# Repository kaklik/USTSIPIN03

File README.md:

## USTSIPIN03 - Semiconductor based ionizing radiation dosimeter and spectrometer analog front-end

The USTSIPIN03 is developed as single board improved variant of the [PIND02](https://github.com/mlab-modules/PIND02) and [PCRD07](https://github.com/mlab-modules/PCRD07) modules from [MLAB.cz development system](https://www.mlab.cz/).  The analog front end is core part of the [AIRDOS04 cosmic radiation detector and dosimeter](https://github.com/UniversalScientificTechnologies/AIRDOS04).

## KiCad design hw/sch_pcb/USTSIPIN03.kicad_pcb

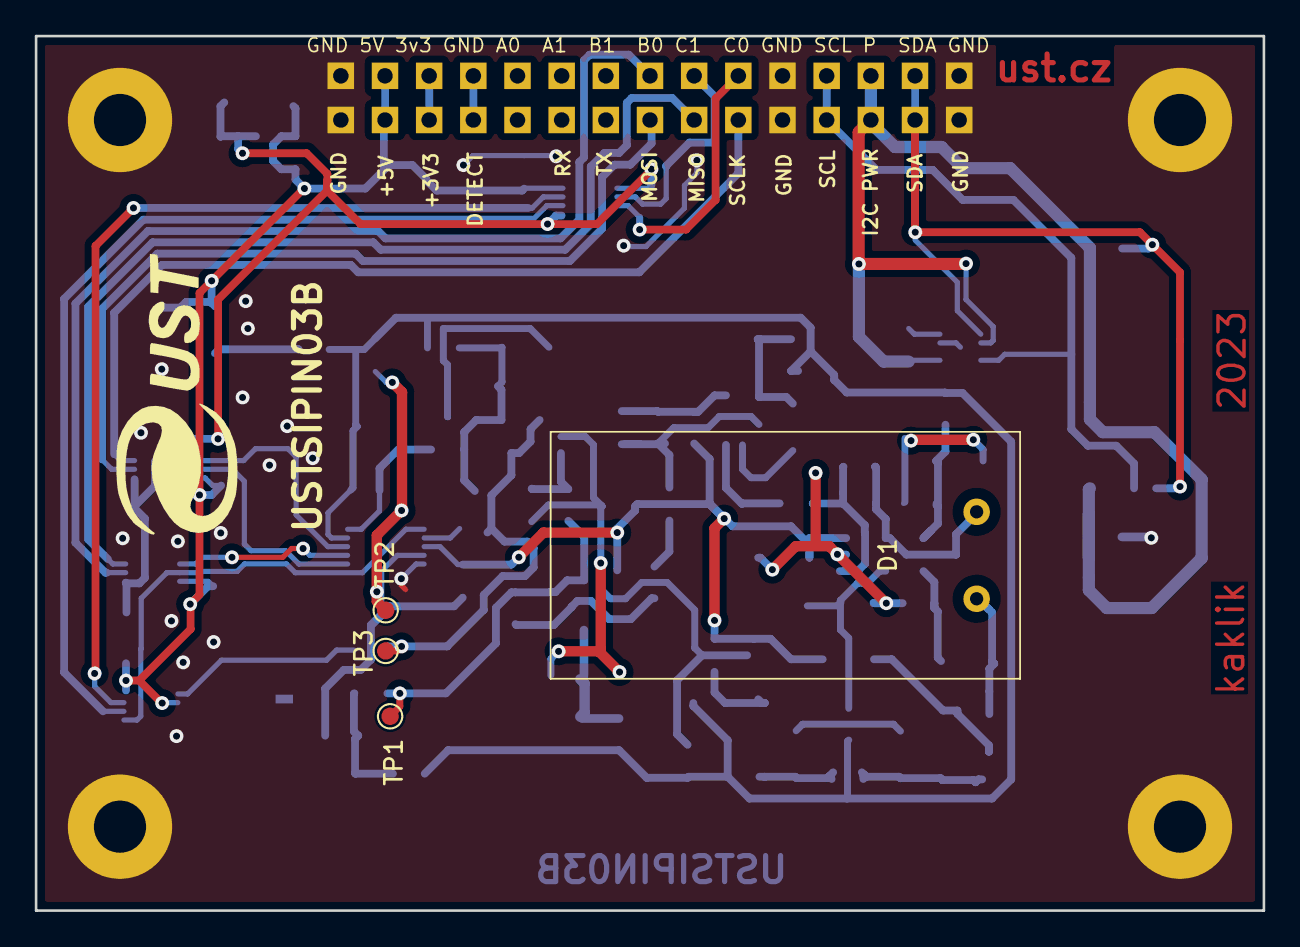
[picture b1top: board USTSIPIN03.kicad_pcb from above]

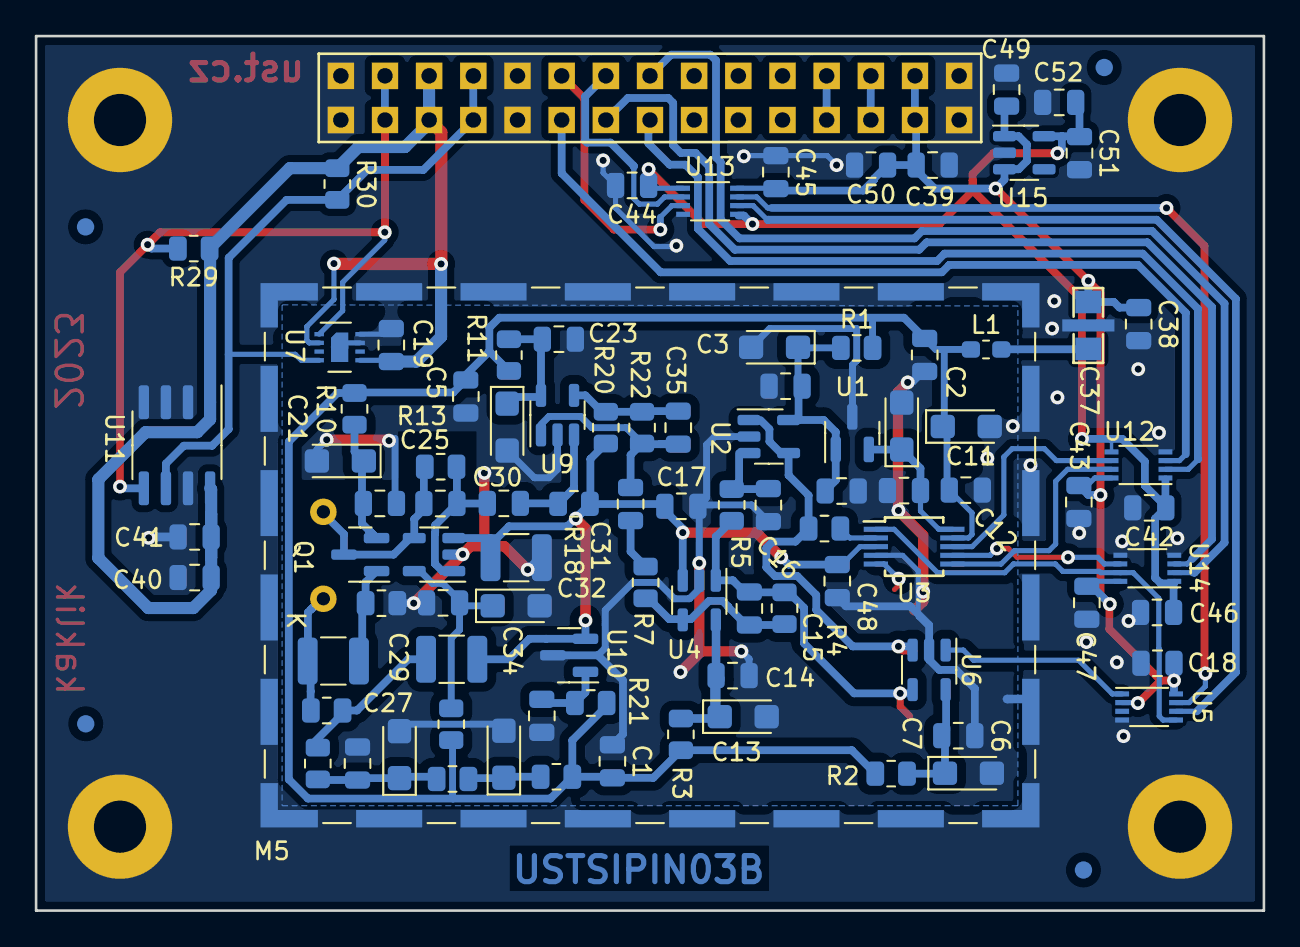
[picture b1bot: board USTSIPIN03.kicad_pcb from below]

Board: 2 copper layers, 70.6 x 50.3 mm, 107 parts (98 on the bottom side), 49 nets.

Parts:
C1, C2, C4, C5, C7, C8, C10, C12, C14, C17, C18, C19, C20, C23, C28, C30, C31, C33, C36, C38, C41, C42, C43, C44, C45, C46, C47, C50, C52: 100nF; C_0805_2012Metric
C3, C6, C9, C11, C13, C21, C24, C26, C27, C34: 10uF; CP_EIA-3216-18_Kemet-A
C15, C35: 3n3; C_0805_2012Metric
C16, C48: 1nF; C_0805_2012Metric
C22, C29, C32: 1uF; C_1210_3225Metric
C25: 1pF; C_0805_2012Metric
C37: 1uF; FIR_0805
C39, C40, C49, C51: 10uF; C_0805_2012Metric
D1: S2744-09; HAMAMATSU_S2744-09
FID1, FID2, FID3, FID4: Fiducial; Fiducial_1mm_Mask2mm
G1: LOGO; UST
J1: HEADER_2x15; Straight_2x15
JP1: Jumper_2_Bridged; NetTie-2_SMD_Pad0.5mm
L1: NL03KT330; L_0603_1608Metric_Pad1.05x0.95mm_HandSolder
M1, M2, M3, M4: HOLE; MountingHole_3mm
M5: RFShield_TwoPieces; Laird_Technologies_BMI-S-210-F_44.00x30.50mm
Q1: 2SK2394-6; SOT-23
R1, R2, R3: 100; R_0805_2012Metric
R4, R5, R18, R20, R29, R30: 10k; R_0805_2012Metric
R6: 10; R_0805_2012Metric
R7, R22: 1k; R_0805_2012Metric
R10, R11, R19, R21: 470R; R_0805_2012Metric
R12, R14, R15, R16, R17: 4k7; R_0805_2012Metric
R13: 10M; R_0805_2012Metric
TP1, TP3: Signal; TestPoint_Pad_D1.0mm
TP2: AGND; TestPoint_Pad_D1.0mm
U1: ISL21080CIH341Z-TK; SOT-23
U2, U4, U9: AD8691; TSOT-23-5
U3: LTC1865-MS; MSOP-10_3x3mm_P0.5mm
U5: SN74LVC2G74; VSSOP-8_2.3x2mm_P0.5mm
U6: TS3021ILT; SOT-23-5
U7: SHT31-DIS; Sensirion_DFN-8-1EP_2.5x2.5mm_P0.5mm_EP1.1x1.7mm
U8: OPA314; SOT-23-5
U10: ISL21080DIH309; SOT-23
U11: AT24CS64-SSHM; SOIC-8_3.9x4.9mm_P1.27mm
U12, U13, U14: SN74LVC2T45DCU; VSSOP-8_2.3x2mm_P0.5mm
U15: MIC5504-3.3YM5-TR; SOT-23-5

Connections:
+3.3V: C42.1, C44.1, C46.1, C51.1, C52.1, U12.1 (VCCA), U12.5 (DIR), U13.1 (VCCA), U13.5 (DIR), U14.1 (VCCA), U15.5 (VOUT)
+5V: C1.1, C2.1, C5.1, C11.1, C12.1, L1.1, R1.2, R2.2, R3.2, R10.2, R11.2, R14.2, R19.2, R21.2, U3.9 (V_{CC})
+5VD: C18.1, C37.3, C38.1, C39.1, C43.1, C45.1, C47.1, C49.1, C50.1, J1.3, J1.4, U5.2 (D), U5.8 (VCC), U12.8 (VCCB), U13.8 (VCCB), U14.8 (VCCB), U15.1 (VIN), U15.3 (EN)
/PIN_detector/A: C25.2, D1.2 (A), Q1.3 (G), R13.2, U8.4 (-)
/PIN_detector/K: C22.2, D1.1 (K), R17.1
/PIN_detector/REF: C17.1, C29.2, C32.1, C48.1, R18.1, R22.2, U3.3 (CH1), U4.3 (+), U8.3 (+), U10.2 (Vout)
/PIN_detector/Signal: C31.1, R7.2
/analogue_backend/4.1 V: C9.1, C10.1, U1.2 (Vout), U3.10 (V_{REF})
/analogue_backend/A/D: R6.1, U3.2 (CH0)
/analogue_backend/CONV: U3.1 (CONV), U5.5 (Q), U14.7 (1B)
/analogue_backend/Reset: U5.6 (~CLR), U13.6 (2B)
/analogue_backend/SCK: U3.8 (SCK), U12.6 (2B)
/analogue_backend/SDI: U3.6 (SDI), U12.7 (1B)
/analogue_backend/SDO: U3.7 (SDO), U14.6 (2B)
/analogue_backend/Set: U5.7 (~PRE), U13.7 (1B)
/analogue_backend/VCC2: C3.1, C4.1, C8.1, R1.1, U1.1 (Vin), U2.5 (V+)
/analogue_backend/VCC3: C6.1, C7.1, R2.1, U6.5 (V+)
/analogue_backend/VCC5: C13.1, C14.1, R3.1, U4.5 (V+)
/interface/3v3: J1.5, J1.6
/interface/B0: J1.15, U14.2 (1A)
/interface/C0: J1.19, U13.3 (2A)
/interface/C1: J1.17, U13.2 (1A)
/interface/SCL: J1.23, J1.24, R30.2, U7.4 (SCL), U11.6 (SCL)
/interface/SDA: J1.27, J1.28, R29.2, U7.1 (SDA), U11.5 (SDA)
/interface/SOCKET_MISO: J1.18, U14.3 (2A)
/interface/SOCKET_MOSI: J1.16, U12.2 (1A)
/interface/SOCKET_SCLK: J1.20, U12.3 (2A)
GND: C11.2, C12.2, C18.2, C19.2, C37.2, C38.2, C39.2, C40.2, C41.2, C42.2, C43.2, C44.2, C45.2, C46.2, C47.2, C49.2, C50.2, C51.2, C52.2, J1.1, J1.2, J1.21, J1.22, J1.29, J1.30, JP1.2, M1.1, M2.1, M3.1, M4.1, M5.1 (Shield), U3.5 (DGND), U5.4 (GND), U7.7 (R), U7.8 (VSS), U7.9 (VSS), U11.2 (A1), U11.3 (A2), U11.4 (GND), U11.7 (WP), U12.4 (GND), U13.4 (GND), U14.4 (GND), U14.5 (DIR), U15.2 (GND)
GNDA: C1.2, C2.2, C3.2, C4.2, C5.2, C6.2, C7.2, C8.2, C9.2, C10.2, C13.2, C14.2, C16.2, C17.2, C20.2, C21.2, C23.2, C24.2, C26.2, C27.2, C28.2, C32.2, C33.2, C34.2, C36.2, C48.2, JP1.1, R12.2, TP2.1, U1.3 (GND), U2.2 (V-), U3.4 (AGND), U4.2 (V-), U6.2 (V-), U8.2 (V-), U9.2 (V-), U10.3 (GND)
unnamed: C25.1, C30.2, R13.1, U8.1
unnamed: C26.1, R14.1, R15.2
unnamed: C27.1, C28.1, R15.1, R16.2
unnamed: C29.1, R16.1, R17.2
unnamed: C31.2, C35.1, R20.1, U9.1
unnamed: C37.1, L1.2
unnamed: J1.7, J1.8
unnamed: C20.1, C21.1, Q1.2 (D), R10.1
unnamed: C22.1, Q1.1 (S), R12.1
unnamed: C16.1, R5.1, U2.3 (+)
unnamed: R6.2, TP3.1, U2.1, U2.4 (-), U6.3 (+)
unnamed: C15.2, R4.2, R7.1, U4.4 (-)
unnamed: U5.1 (C), U6.1
unnamed: C15.1, R4.1, R5.2, TP1.1, U4.1, U6.4 (-)
unnamed: C33.1, C34.1, R19.1, U8.5 (V+)
unnamed: C30.1, R18.2, U9.3 (+)
unnamed: C35.2, R20.2, R22.1, U9.4 (-)
unnamed: C23.1, C24.1, R11.1, U9.5 (V+)
unnamed: C36.1, R21.1, U10.1 (Vin)
VDD: C19.1, C40.1, C41.1, J1.25, J1.26, R29.1, R30.1, U7.2 (ADDR), U7.5 (VDD), U11.1 (A0), U11.8 (VCC)

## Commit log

2023-11-12 Renaming AIRDOS04 base board to sensor board.
2023-11-12 Fix rename and improve silkscreen.
2023-11-12 Render previews Add testpoints.
2023-11-12 change solder mask expansion and revise DRC.
2023-11-12 Review ERC issues.
2023-11-12 Initial commit of detector design.
2023-11-12 Add github actions.
2023-11-12 Update workflow files
2023-11-12 Update actions products
2023-11-13 Update silkscreen and title blocks.
2023-11-13 Fix USTID
2023-11-16 FIX USTIDs.
2023-11-19 Add notes to power consumption.
2023-11-20 Update PCB from schematics.
2023-11-20 Edit logo reference value.
2023-11-20 Create LICENSE
2023-11-27 Flip side of pinheader connector. Resolve #7
2023-11-27 Swap power pins of input OpAMP. Reslove #6
2023-11-27 Swap MISO and MOSI traces. Resolve #4
2023-11-27 Attempt to improve #2.
2023-11-27 Add LDO to power 3.3V translators. Resolve #3
2023-11-27 Removed hand-soldering footprints for OpAmps. Rosolve #1
2023-11-27 Unmask only a sourroundings of sensing diode. Resolve #2
2023-11-27 Improve solder mask covering under sensing diode.
2023-12-05 Update PCB design title block.
2023-12-05 Uniform capacitor types.
2023-12-24 Remove black border from the images.
2024-05-30 Update Kicad project version.
